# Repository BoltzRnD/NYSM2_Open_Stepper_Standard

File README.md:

# NYSM.2 Open Stepper Standard
## Not Your Standard M.2
### "Not Your Standard M.2" is literally not your standard m.2 interface, and is a new open-source stepper motor driver board that utilizes the M.2 interface to control motors using the TMCxx and all other stepper drivers.

Modular stepper drivers are far superior than traditional pololu footprints as it has

1. Poka-yoke installations: The Key's in the interfaces makes sure that you never mess up installation orientations of the driver

apart from this NYSM.2 extends beyond these to provide more features as below:

1. physical locking mechanisms: to make sure drivers are locked in when In operation.

2. Horizontal installation: instead of vertical mounting, to not only save space in Z axis, but to also make the system less fragile to accidental damage if stuck by a physical shock.

3. Top and Bottom Installations: since NYSM.2 utilizes SMD and single layer mounted connectors, it means that it is possible to add by design 2 NYSM.2 modules in the same footprint area, drastically reducing the required footprint for more drivers - i.e - 20 drivers in 10 drivers area by installing 10 on top layer and 10 on bottom.

4. highly cost effective: since M.2 is a widely available standard with high MOQs already flooding the industry, the M.2 connectors can be integrated at very low costs into your design, where the stepper card doesn't even need a connector as it uses an edge connector built into the PCB only. in comparison to other modular standards that uses custom repurposed obsolete connector that has low manufacturing volumes. With NYSM.2 we can adopt a modular standard at almost same cost of a traditional pololu stepper drivers.

5. Powerful in terms of power: NYSM.2 utilizes 8 contacts(0.5A per pin) per power connection to deliver a whopping **4A** to the motors, that too at **24V**, that totals to **96W** per driver.
moreover it is theoretically possible to get more power out of it by increasing the voltages.

But that is not the best thing about NYSM.2 standard, the only best thing about it is only and only it's open source nature and GPL V3 license, that allows creators, hobbyist and manufacturers worldwide to move to a new and open modular stepper driver interface standard.
unlike other modular stepper interfaces, this interface is open inside out, and is not designed to lock you into single specific manufacturer's ecosystem. and is made for the world to use.

## The NYSM.2 Standard Pinout Format

## Pinout Table

| Pin Name   | Pin Number | Description                             
|------------|------------|-----------------------------------------|
| EN         | 1          | Enable/Disable Stepper Driver
| MS1        | 3          | Microstep Selection Pin 1 / CFG1 / SDI
| MS2        | 5          | Microstep Selection Pin 2 / CFG2 / SCK
| UART_TX    | 7          | UART Transmission (Communication) / CFG 3 / CS
| UART_RX    | 9          | UART Receive (Communication) / CFG0 / SDO
| CLK        | 11          | CLK input       
| STEP       | 21          | STEP input            
| DIR        | 23          | DIR input 
| GND        | 25          | Ground                   
| VCC_IO     | 27         | 3.3V to 5V IO supply voltage for all digital pins (does not supply IC logic part).
| GND        | 29         | Ground               
| VREF       | 31         | Analog reference voltage for current scaling or reference current for use of internal sense resistors
| DIAG       | 33         | Diagnostic and StallGuard output
| INDEX      | 35         | Configurable index output. Provides index pulse.
| SPREAD     | 37         | Chopper mode selection: Low=StealthChop, High=SpreadCycle (may be left unconnected)
| STDBY      | 39         | STANDBY input  
| GND        | 45, 47, 49, 51, 53, 55, 57, 59 | Ground/PSU Negative (0.5A per pin, 4A Total)
| POW_MOT    | 61, 63, 65, 67, 69, 71, 73, 75 | Motor supply voltage (0.5A per pin, 4A Total)
| A2         | 4, 6, 8, 10, 20, 22, 24, 26 | Motor coil A output 2 (0.5A per pin, 4A Total)
| A1         | 28, 30, 32, 34, 36, 38, 40, 42 | Motor coil A output 1 (0.5A per pin, 4A Total)
| B1         | 44, 46, 48, 50, 52, 54, 56, 58 | Motor coil B output 1 (0.5A per pin, 4A Total)
| B2         | 60, 62, 64, 66, 68, 70, 72, 74 | Motor coil B output 2 (0.5A per pin, 4A Total)

# Manufacturing and other design considerations

Please take special care to follow these points when manufacturing the NYSM2 Boards
1. Board Thickness - 0.8mm (Standard M.2 Board Thickness)
2. Gold Plating is preferred but not Necessary.
3.  **This Version of the board omits the use of current limit series phase resistors, in case it is a necessity for your design, Please use the design from Branch alt_sense**
4. Short The onboard jumper to use the potentiometer for standalone mode.
5. Use a generic Raspberry Pi or other 25x25mm heatsinks on top.

# License
NYSM.2 standard pinout and NYSM.2 TMC2209 Board contributed by Boltz R&D is licensed under GPL V3 license, and is owned by the community and everyone.
Also while the standard is open(i.e - The standard pinout sequence on M.2 Key B and it's derivatives only, that means proprietary manufacturers needs to be compliant to GPLV3 for only the pinout.),
you can integrate it into your proprietary designs as long as the NYSM.2 section of your design respects the license.
We invite all creators, hobbyist, and manufacturers to utilize the standard and the design.

# Key Features for this NYSM.2 TMC2209 Board:
* NYSM.2 Interface: Compact, modular design that fits into M.2 slots, making it easy to install and maintain.
* TMC2209 Stepper Driver: One of the Industry-leading drivers for stepper motors, featuring sensorless homing, stall detection, and ultra-quiet operation.

## Assembly and Setup

1. **Step 1**: Insert the **NYSM.2** board into an M.2 slot.
2. **Step 2**: Connect your stepper motor wires to the appropriate output terminals.
3. **Step 3**: Configure your firmware (e.g., **Marlin** or **Klipper**) to control the TMC2209 driver.
4. **Step 4**: Power on the system, and your motors are ready.

## Firmware Changes
1.In klipper change set step_pulse_duration to 0.000000400 or more, in case you face print misallignment or continous layer shifting.
- Reason: Apparently if you are using the EVAL board with NYSM.2, when using klipper and in UART mode, the firmnware switches to pulse timing of 100ns which causes step and dir to overlap sometimes over long cables, anyways 100ns was already an overkill since in standalone mode the pulse duration defaults to 2uS. this shouldn't happen with installations of NYSM.2 standard where the socket is on the mainboard itself

## Getting Started on Development:

Clone the repository:  
`git clone https://github.com/BoltzRnD/NYSM2_Open_Stepper_Standard`

# Join the Community
We are actively looking for contributors to help us enhance this project. You can join our community to discuss ideas, report bugs, or request features:

- **Discord**: [Join us here](https://discord.gg/xWGaHd83Hs)
- **Email**: info@boltzrnd.com

# Future Plans
- **Custom Heatsink Designs**.
- **Extended Compatibility**: support for other stepper driver like TMC5160 and TMC2130.

# Disclaimer
The **NYSM.2 standard and NYSM.2 board** is provided as-is without any warranties. Boltz R&D is not responsible for any damages or issues that may arise from the use of this board.

    NYSM.2 standard
    Copyright (C) 2024 Boltz R&D

    This Project/Open Standard is free: you can redistribute it and/or modify
    it under the terms of the GNU General Public License as published by
    the Free Software Foundation, either version 3 of the License, or
    (at your option) any later version.

    This is distributed in the hope that it will be useful,
    but WITHOUT ANY WARRANTY; without even the implied warranty of
    MERCHANTABILITY or FITNESS FOR A PARTICULAR PURPOSE.  See the
    GNU General Public License for more details.

    You should have received a copy of the GNU General Public License
    along with this program.  If not, see <https://www.gnu.org/licenses/>.

Contact : info@boltzrnd.com

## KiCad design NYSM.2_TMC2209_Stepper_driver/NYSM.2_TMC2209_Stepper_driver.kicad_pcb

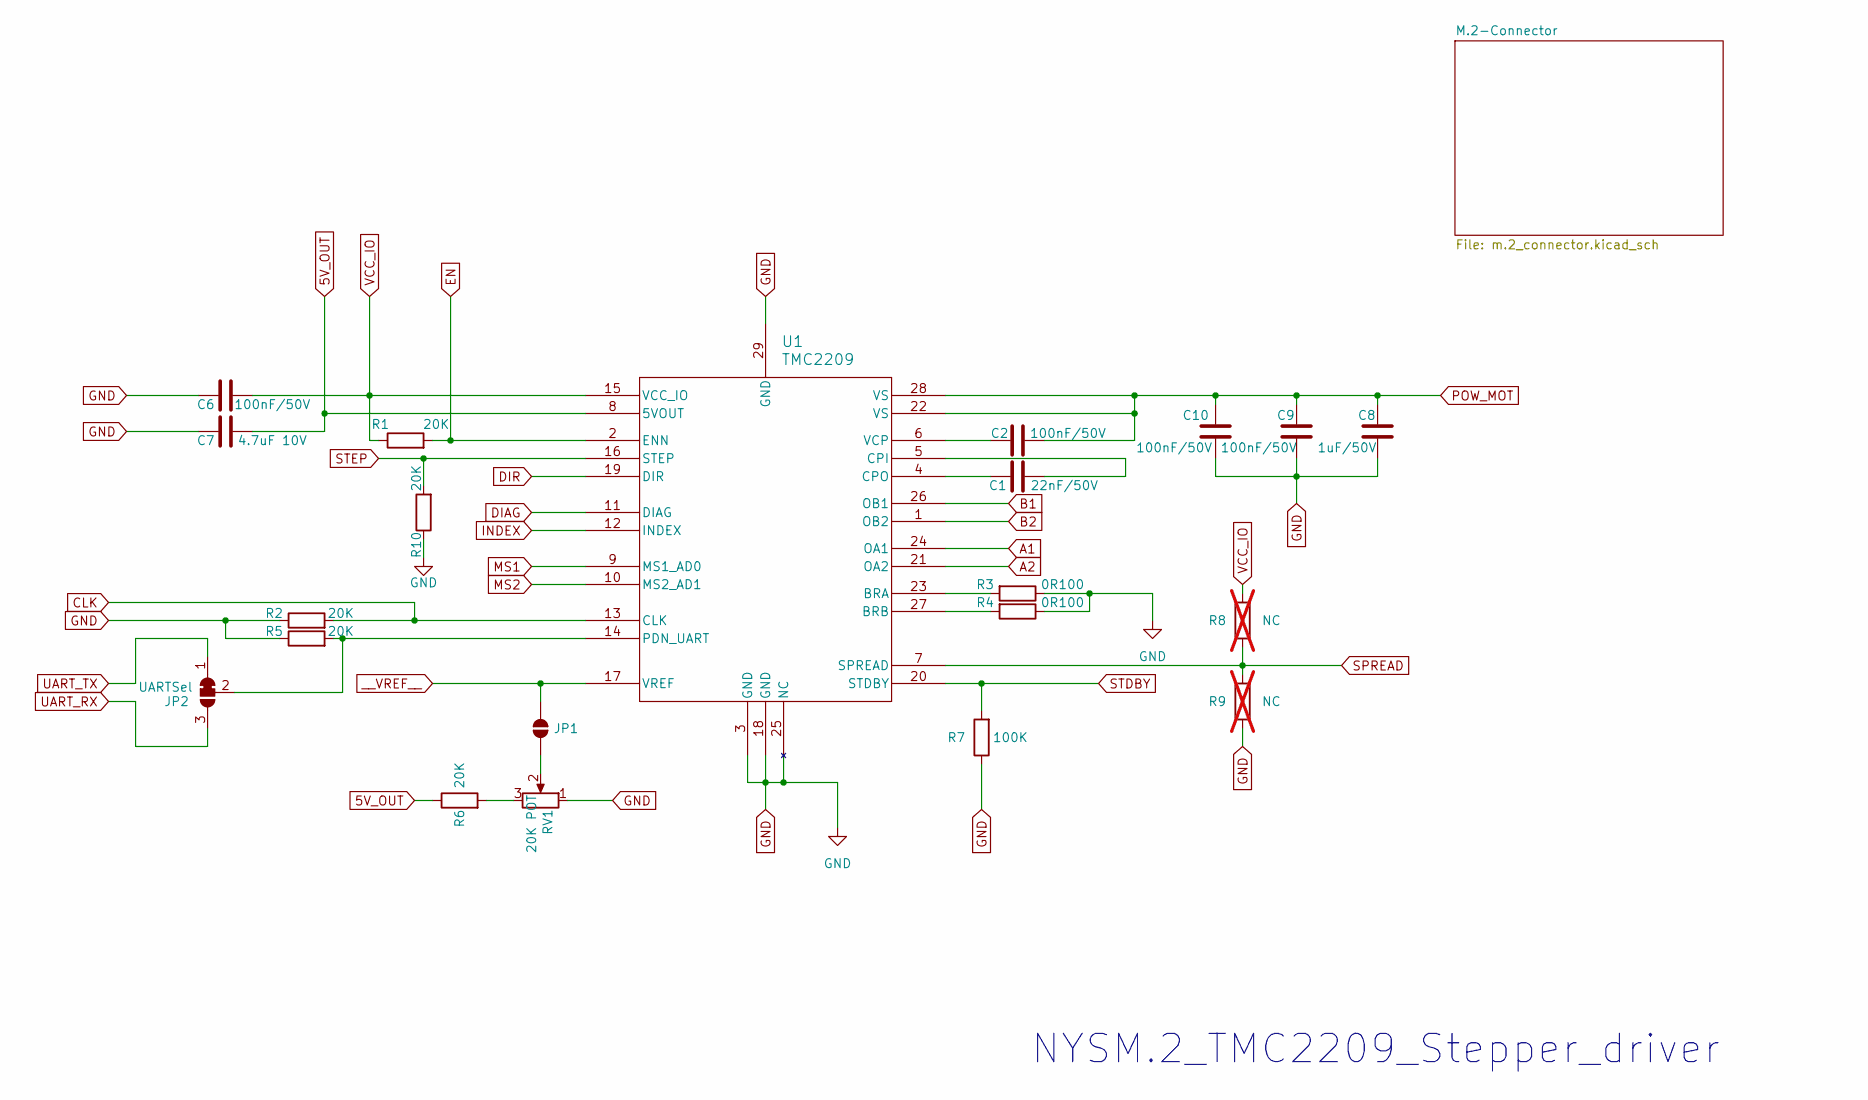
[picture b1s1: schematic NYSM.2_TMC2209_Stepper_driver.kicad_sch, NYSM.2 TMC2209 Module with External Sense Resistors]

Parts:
C1: 22nF/50V; C_0402_1005Metric; Manufacturer_Part_Number CC0402KRX7R9BB223; LCSC# C107026
C2, C6, C9, C10: 100nF/50V; C_0402_1005Metric; Manufacturer_Part_Number 0402B104K500CT; LCSC# C152814
C7: 4.7uF 10V; C_0402_1005Metric; Manufacturer_Part_Number CL05A475KP5NRNC; LCSC# C368809
C8: 1uF/50V; C_0402_1005Metric; Manufacturer_Part_Number GRM155R61H105KE05D; LCSC# C1518208
JP1: SolderJumper-2_P1.3mm_Open_Pad1.0x1.5mm
JP2: UARTSel; SolderJumper-3_P1.3mm_Bridged12_RoundedPad1.0x1.5mm
R1, R2, R5, R6, R10: 20K; R_0402_1005Metric; Manufacturer_Part_Number WR04X203JTL; LCSC# C384364
R3, R4: 0R100; R_1206_3216Metric; Manufacturer_Part_Number PT1206FR-7W0R1L; LCSC# C3033268
R7: 100K; R_0402_1005Metric; Manufacturer_Part_Number WR04X104JTL; LCSC# C384388
R8, R9: NC; R_0402_1005Metric; not fitted
RV1: 20K POT; Potentiometer_Bourns_TC33X_Vertical; Manufacturer_Part_Number VG039NCHXTB203; LCSC# C128550
U1: TMC2209; QFN28_5X5_TRI; Manufacturer_Part_Number TMC2209; LCSC# C465949

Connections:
5V_OUT: C7.2, R6.1, U1.8 (5VOUT)
A1: U1.24 (OA1); also elsewhere on the board
A2: U1.21 (OA2); also elsewhere on the board
B1: U1.26 (OB1); also elsewhere on the board
B2: U1.1 (OB2); also elsewhere on the board
CLK: R2.2, U1.13 (CLK); also elsewhere on the board
DIAG: U1.11 (DIAG); also elsewhere on the board
DIR: U1.19 (DIR); also elsewhere on the board
EN: R1.2, U1.2 (ENN); also elsewhere on the board
GND: C6.1, C7.1, C8.2, C9.2, C10.2, R2.1, R3.1, R4.1, R5.1, R7.1, R9.1, R10.1, RV1.1, U1.3 (GND), U1.18 (GND), U1.25 (NC), U1.29 (GND); also elsewhere on the board
INDEX: U1.12 (INDEX); also elsewhere on the board
MS1: U1.9 (MS1_AD0); also elsewhere on the board
MS2: U1.10 (MS2_AD1); also elsewhere on the board
unnamed: JP1.1 (A), RV1.2
unnamed: JP2.2 (C), R5.2, U1.14 (PDN_UART)
unnamed: R6.2, RV1.3
unnamed: R3.2, U1.23 (BRA)
unnamed: R4.2, U1.27 (BRB)
unnamed: C1.2, U1.5 (CPI)
unnamed: C1.1, U1.4 (CPO)
unnamed: C2.1, U1.6 (VCP)
POW_MOT: C2.2, C8.1, C9.1, C10.1, U1.22 (VS), U1.28 (VS); also elsewhere on the board
SPREAD: R8.1, R9.2, U1.7 (SPREAD)
STDBY: R7.2, U1.20 (STDBY); also elsewhere on the board
STEP: R10.2, U1.16 (STEP); also elsewhere on the board
UART_RX: JP2.3 (B); also elsewhere on the board
UART_TX: JP2.1 (A); also elsewhere on the board
VCC_IO: C6.2, R1.1, R8.2, U1.15 (VCC_IO); also elsewhere on the board
__VREF__: JP1.2 (B), U1.17 (VREF); also elsewhere on the board

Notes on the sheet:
NYSM.2_TMC2209_Stepper_driver

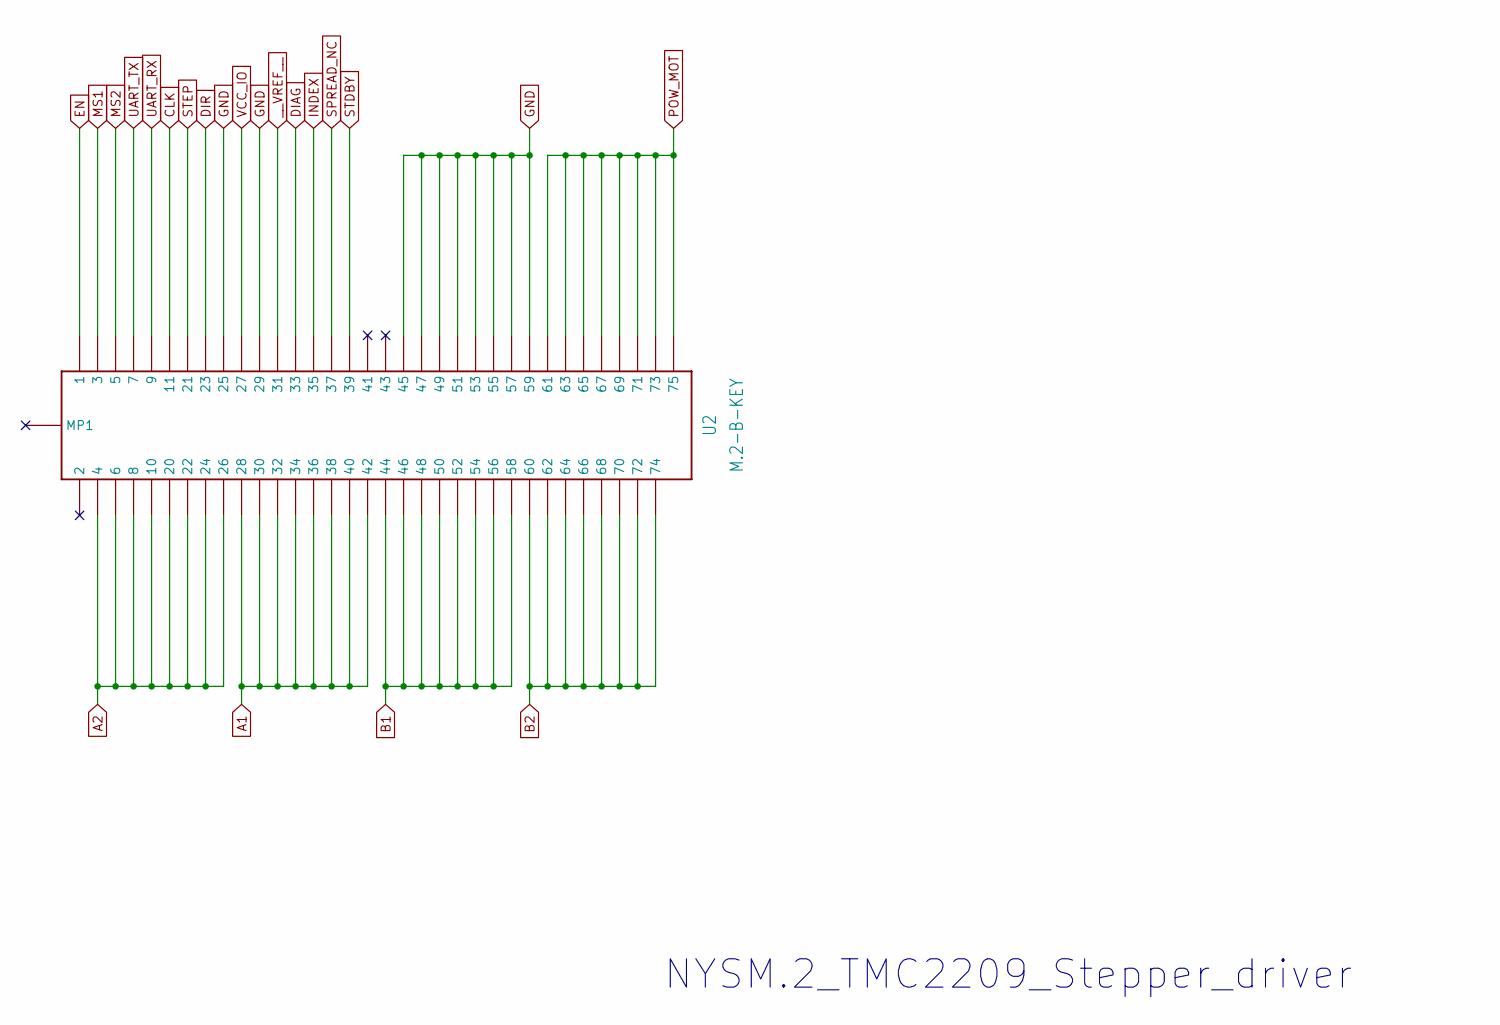
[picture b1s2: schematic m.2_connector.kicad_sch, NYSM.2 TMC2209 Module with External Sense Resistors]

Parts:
U2: M.2-B-KEY; NYSM2-Card-B-Key

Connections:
A1: U2.P$28 (28), U2.P$30 (30), U2.P$32 (32), U2.P$34 (34), U2.P$36 (36), U2.P$38 (38), U2.P$40 (40), U2.P$42 (42); also elsewhere on the board
A2: U2.P$4 (4), U2.P$6 (6), U2.P$8 (8), U2.P$10 (10), U2.P$20 (20), U2.P$22 (22), U2.P$24 (24), U2.P$26 (26); also elsewhere on the board
B1: U2.P$44 (44), U2.P$46 (46), U2.P$48 (48), U2.P$50 (50), U2.P$52 (52), U2.P$54 (54), U2.P$56 (56), U2.P$58 (58); also elsewhere on the board
B2: U2.P$60 (60), U2.P$62 (62), U2.P$64 (64), U2.P$66 (66), U2.P$68 (68), U2.P$70 (70), U2.P$72 (72), U2.P$74 (74); also elsewhere on the board
CLK: U2.P$11 (11); also elsewhere on the board
DIAG: U2.P$33 (33); also elsewhere on the board
DIR: U2.P$23 (23); also elsewhere on the board
EN: U2.P$1 (1); also elsewhere on the board
GND: U2.P$25 (25), U2.P$29 (29), U2.P$45 (45), U2.P$47 (47), U2.P$49 (49), U2.P$51 (51), U2.P$53 (53), U2.P$55 (55), U2.P$57 (57), U2.P$59 (59); also elsewhere on the board
INDEX: U2.P$35 (35); also elsewhere on the board
MS1: U2.P$3 (3); also elsewhere on the board
MS2: U2.P$5 (5); also elsewhere on the board
POW_MOT: U2.P$61 (61), U2.P$63 (63), U2.P$65 (65), U2.P$67 (67), U2.P$69 (69), U2.P$71 (71), U2.P$73 (73), U2.P$75 (75); also elsewhere on the board
SPREAD_NC: U2.P$37 (37)
STDBY: U2.P$39 (39); also elsewhere on the board
STEP: U2.P$21 (21); also elsewhere on the board
UART_RX: U2.P$9 (9); also elsewhere on the board
UART_TX: U2.P$7 (7); also elsewhere on the board
VCC_IO: U2.P$27 (27); also elsewhere on the board
__VREF__: U2.P$31 (31); also elsewhere on the board

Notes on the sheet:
NYSM.2_TMC2209_Stepper_driver

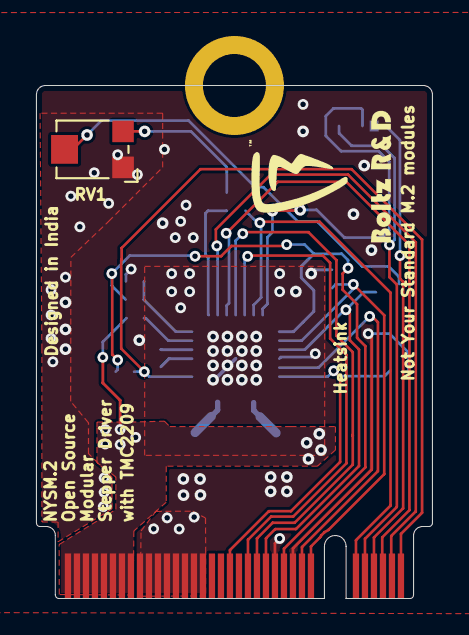
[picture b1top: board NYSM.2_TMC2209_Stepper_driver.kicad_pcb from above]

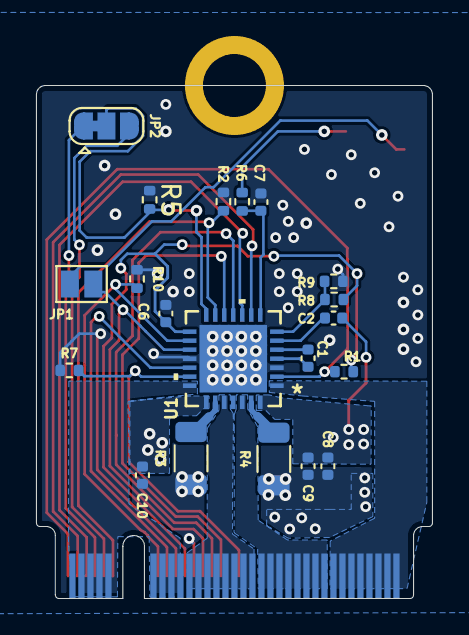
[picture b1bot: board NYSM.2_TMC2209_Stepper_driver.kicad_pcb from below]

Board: 2 copper layers, 22.0 x 28.5 mm, 22 parts (20 on the bottom side), 29 nets.

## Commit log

2024-10-27 Added Files for Release of NYSM2
2024-11-03 Update README.md with manufacturing considerations
2024-11-08 Preliminary push for alternative version with External Sense Resistors
2024-12-14 Added production Files
2024-12-14 added BOM
2025-03-20 Update README.md
    info for alternative design with sense resistors
2025-12-21 Add firmware changes for Klipper configuration
    Added firmware changes section with specific configuration details for Klipper and EVAL board.
2025-12-21 Update README with firmware changes for Klipper
    Added firmware configuration advice for Klipper and TMC2209 driver to README.
2025-12-21 Add warning about current limit resistors omission
    Added a warning about the omission of current limit resistors in the board design.

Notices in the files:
NYSM.2_TMC2209_Stepper_driver/NYSM.2_TMC2209_Stepper_driver.kicad_sch:
License: This work is licensed under GPLV3
